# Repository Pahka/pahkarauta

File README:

Pahka home automation hardware (c) 2012 Teemu Hakala <temmi@iki.fi>

directory structure:

PETnode_basic/
    Pahka Ethernet Terminus node with a bell
    STM32F100 ENC28J60

PETnode_minimal/
    Pahka Ethernet Terminus node
    STM32F100 ENC28J60

PETnode_super/
    Pahka Ethernet Terminus node with bells and whistles and gongs
    STM32F104

important_downloaded_files_from_other_sources/
    documentation, libraries etc
    (c) their respective owners

risut/
    Pahka demo platform submodules in deadbug splatter style or something

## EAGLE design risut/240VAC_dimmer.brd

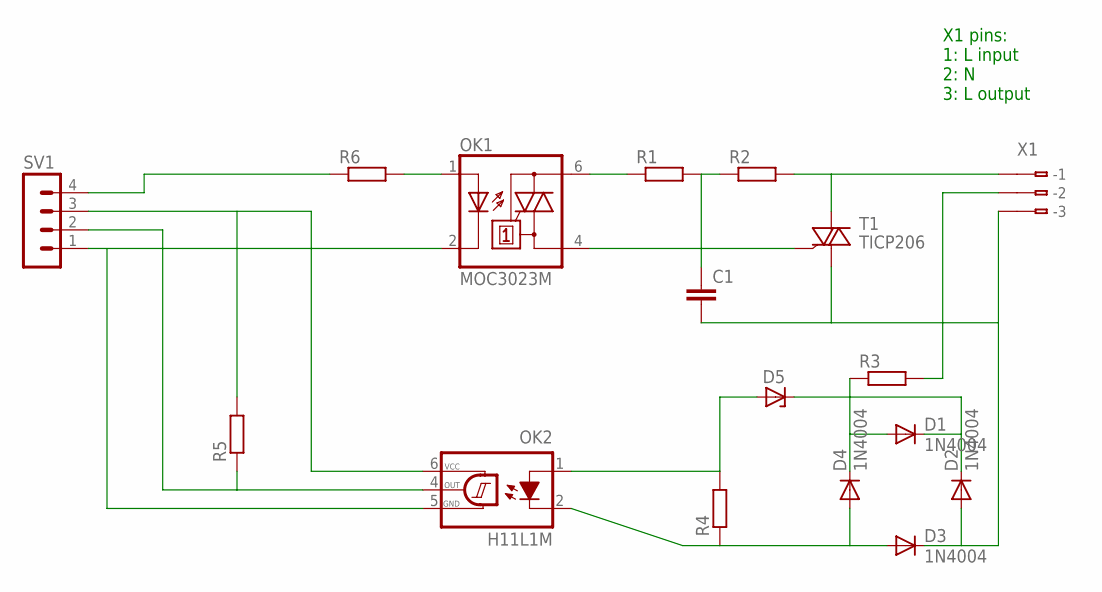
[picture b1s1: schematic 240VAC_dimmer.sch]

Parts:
C1: C-EU050-030X075; C050-030X075
D1, D2, D3, D4: 1N4004; DO41-10
D5: ZENER-DIODEDO41Z10; DO41Z10
OK1: MOC3023M; DIL06
OK2: H11L1M; DIL06
R1, R2: R-EU_0411/12; 0411/12
R3: R-EU_0207/10; 0207/10
R4, R5, R6: R-EU_0204/7; 0204/7
SV1: MA04-1
T1: TICP206; TO92-6
X1: 233-103

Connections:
unnamed: OK1.6 (A2), R1.1
unnamed: C1.1, R1.2, R2.1
unnamed: R2.2, T1.A2, X1.B1 (B-1)
unnamed: OK1.4 (A1), T1.G
unnamed: C1.2, D2.A, D3.C, T1.A1, X1.B3 (B-3)
unnamed: D1.A, D4.C, R3.1
unnamed: D3.A, D4.A, OK2.2 (C), R4.1
unnamed: D5.A, OK2.1 (A), R4.2
unnamed: D1.C, D2.C, D5.C
unnamed: OK1.2 (C), OK2.5 (GND), SV1.1
unnamed: OK2.4 (OUT), R5.1, SV1.2
unnamed: OK2.6 (VCC), R5.2, SV1.3
unnamed: OK1.1 (A), R6.2
unnamed: R6.1, SV1.4
unnamed: R3.2, X1.B2 (B-2)

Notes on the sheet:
X1 pins: 1: L input 2: N 3: L output

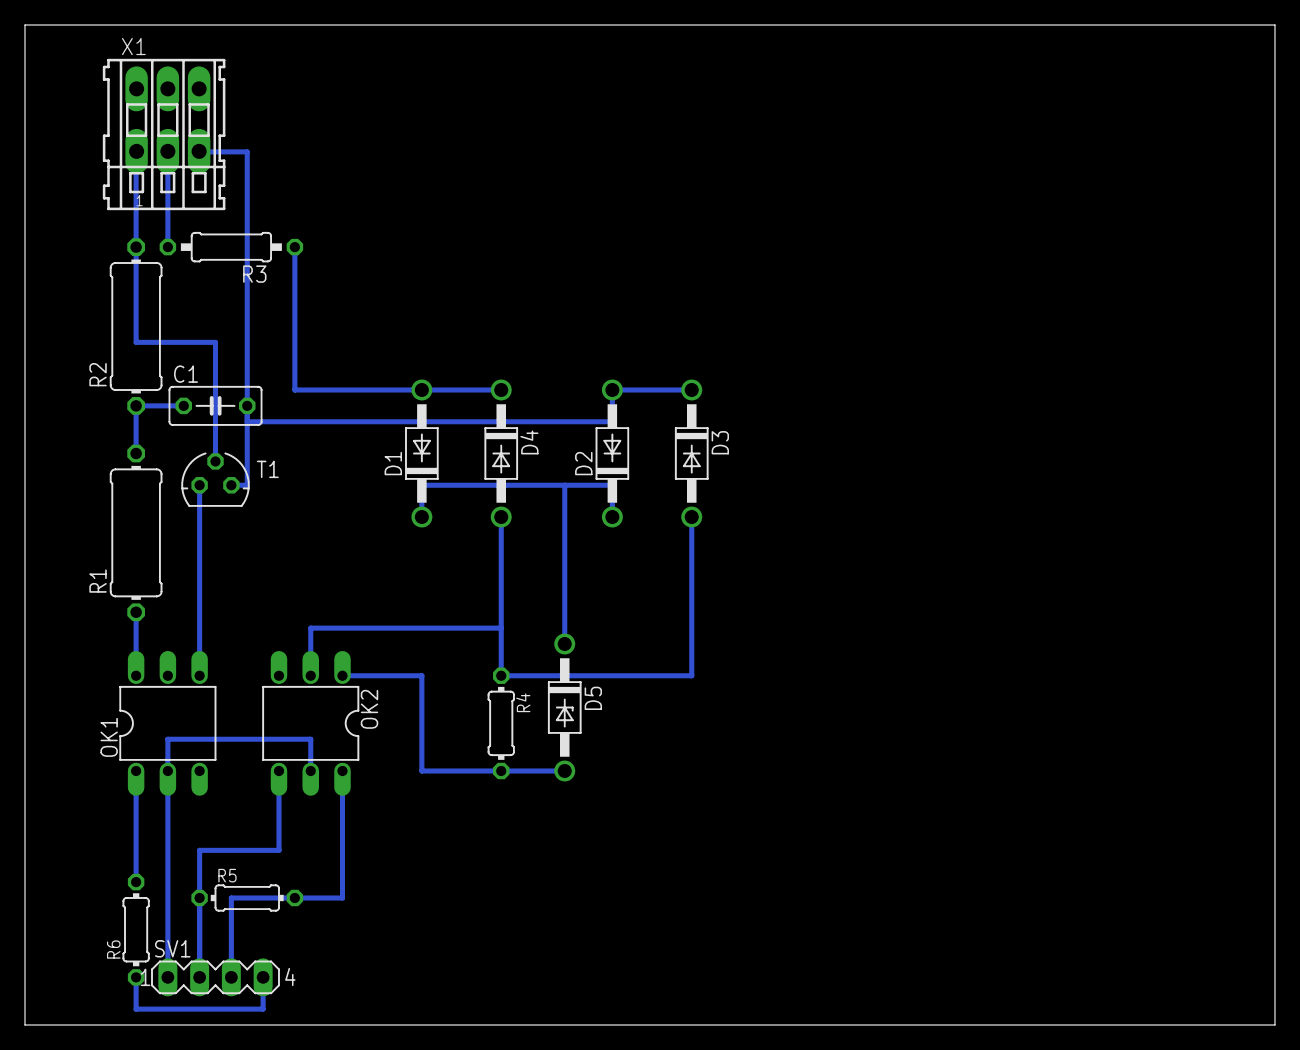
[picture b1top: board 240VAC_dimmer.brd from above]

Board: 2 copper layers, 100.0 x 80.0 mm, 17 parts (0 on the bottom side), 15 nets.

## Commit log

2012-12-03 wrote some design documentation
2012-12-04 added a folder for deadbug demo stuff
2012-12-04 added a folder for third party sourced files
2012-12-06 added PETnode_basic as a plain folder
2012-12-06 rm Pahka node basic motherboard.s#*
2012-12-06 zero crossing notes
2012-12-06 added H11L1 datasheet
2012-12-06 schematic of the dimmer is nearly ready
2012-12-06 fixed a bug, added comments
2012-12-06 added a screenshot of the dimmer
2012-12-06 fixed a bug in dimmer: X1 pin configuration was wrong
2012-12-07 first draft of a pcb layout
2013-01-12 added some illustrative curves for the triac dimmer
2013-01-12 fixed the periodicalness for triac graphs
2013-01-12 a nice animation for parameter a
2013-01-12 fixed mistake so that both sine halves are treated properly
2013-01-12 a prettier pdf
